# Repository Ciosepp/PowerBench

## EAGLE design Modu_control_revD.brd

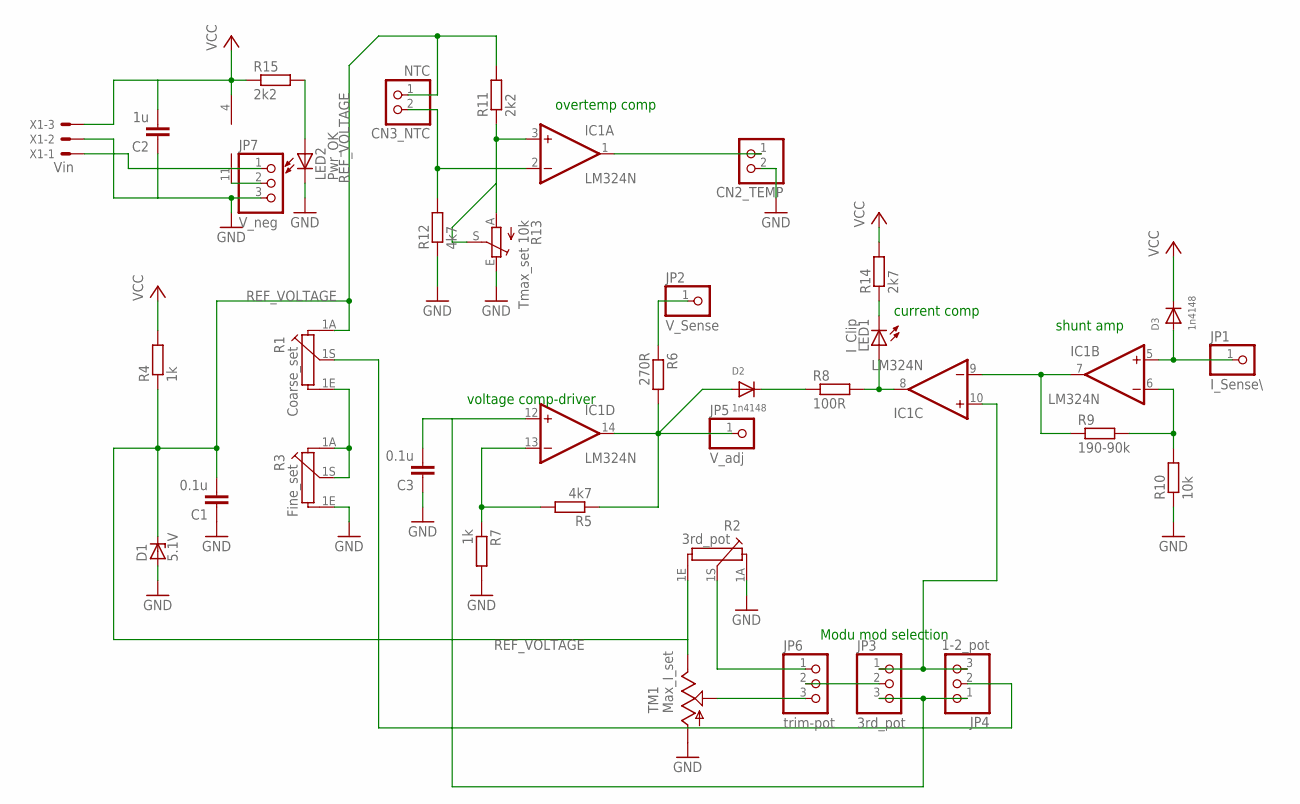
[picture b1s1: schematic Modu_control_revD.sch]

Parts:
C1, C3: 0.1u; C050-025X075
C2: 1u; C050-025X075
CN2_TEMP: JST_2PIN-THM; JST-PH-2-THM
CN3_NTC: NTC; JST-PH-2-THM
D1: 5.1V; DO35Z10
D2, D3: 1n4148; DO-1N4148
IC1: LM324N; DIL14
JP1: I_Sense\; 1X01
JP2: V_Sense; 1X01
JP3: 3rd_pot; 1X03
JP4: 1-2_pot; 1X03
JP5: V_adj; 1X01
JP6: trim-pot; 1X03
JP7: V_neg; 1X03
LED1: I_Clip; LED3MM
LED2: Pwr_OK; LED3MM
R1: Coarse_set; PC16S
R2: 3rd_pot; PC16S
R3: Fine_set; PC16S
R4: 1k; 0207/10
R5, R12: 4k7; 0204V
R6: 270R; 0204V
R7: 1k; 0204/7
R8: 100R; 0204V
R9: 190-90k; 0204V
R10: 10k; 0204/7
R11: 2k2; 0204/7
R13: Tmax_set 10k; B25P
R14: 2k7; 0204V
R15: 2k2; 0204V
TM1: Max_I_set; 6MM
X1: Vin; JST-XH-03-PACKAGE-LONG-PAD

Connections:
GND: C1.1, C2.1, C3.1, CN2_TEMP.2 (1), D1.A, JP7.3, LED2.K (C), R2.1A, R3.1E, R7.2, R10.1, R12.1, R13.E, TM1.A, X1.2
unnamed: CN2_TEMP.1 (2), IC1.1 (OUT)
unnamed: CN3_NTC.2 (1), IC1.2 (-IN), R12.2
unnamed: IC1.13 (-IN), R5.2, R7.1
unnamed: D2.A, IC1.14 (OUT), JP5.1, R5.1, R6.2
unnamed: JP2.1, R6.1
unnamed: R1.1E, R3.1A, R3.1S
unnamed: C3.2, IC1.12 (+IN), JP3.3, JP4.1
unnamed: D2.C, R8.1
unnamed: IC1.8 (OUT), LED1.A, R8.2
unnamed: D3.A, IC1.5 (+IN), JP1.1
unnamed: IC1.6 (-IN), R9.2, R10.2
unnamed: IC1.7 (OUT), IC1.9 (-IN), R9.1
unnamed: IC1.10 (+IN), JP3.1, JP4.3
unnamed: LED1.K (C), R14.1
unnamed: JP6.3, TM1.S
unnamed: IC1.3 (+IN), R11.1, R13.A, R13.S
unnamed: JP3.2, JP6.2
unnamed: JP6.1, R2.1S
unnamed: IC1.11 (V-), JP7.2
unnamed: JP4.2, R1.1S
unnamed: JP7.1, X1.1
unnamed: LED2.A, R15.2
REF_VOLTAGE: C1.2, CN3_NTC.1 (2), D1.C, R1.1A, R2.1E, R4.1, R11.2, TM1.E
VCC: C2.2, D3.C, IC1.4 (V+), R4.2, R14.2, R15.1, X1.3

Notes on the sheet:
Modu mod selection
shunt amp
current comp
voltage comp-driver
overtemp comp

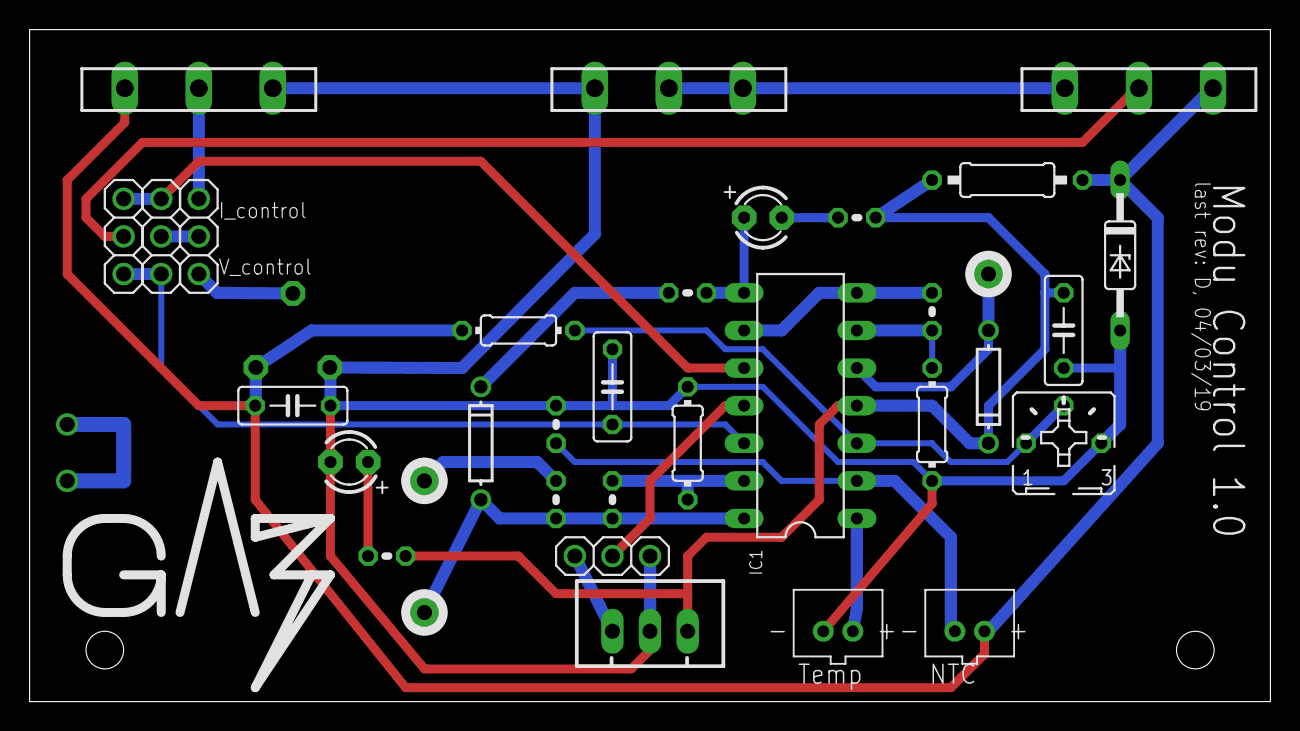
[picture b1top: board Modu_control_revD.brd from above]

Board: 2 copper layers, 83.8 x 45.4 mm, 35 parts (1 on the bottom side), 25 nets.

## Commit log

2019-03-11 Added rev.D pcb files
